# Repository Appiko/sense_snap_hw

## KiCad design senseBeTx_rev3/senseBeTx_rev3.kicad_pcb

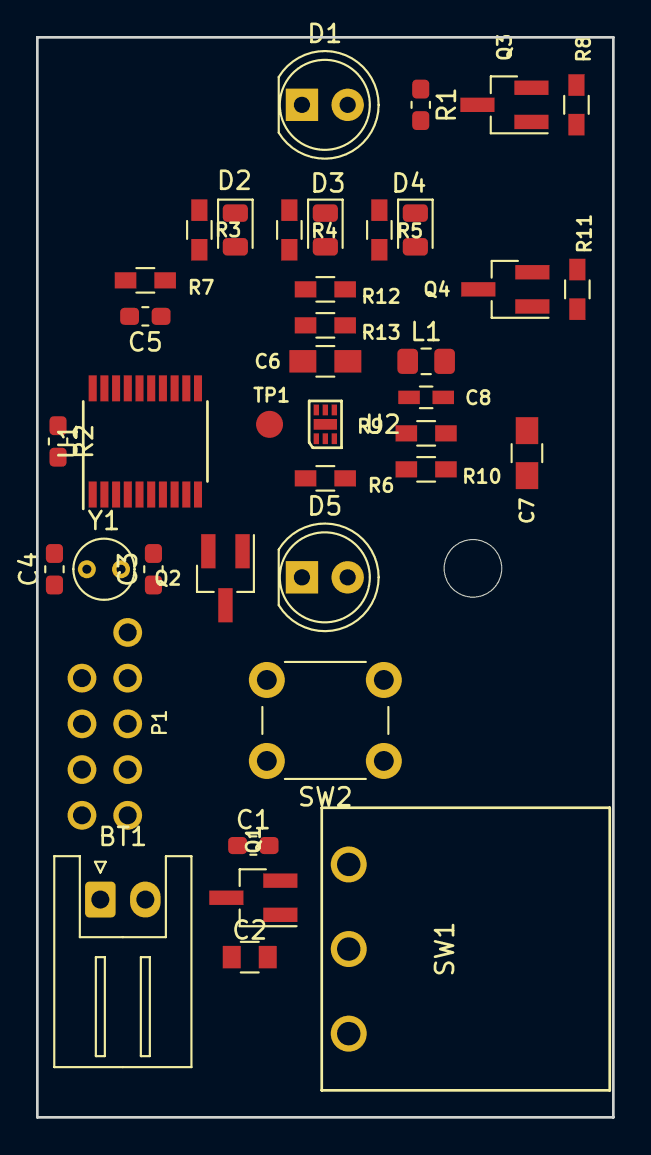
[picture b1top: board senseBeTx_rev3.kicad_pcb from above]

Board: 2 copper layers, 32.0 x 60.0 mm, 41 parts (1 on the bottom side), 30 nets, no tracks yet.

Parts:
BT1: Battery; 2462_BatteryHolder_AAx2
BT1#2: Battery; JST_XH_S02B-XH-A_1x02_P2.50mm_Horizontal
C1, C5: 100nF; C_0603_1608Metric_Pad1.05x0.95mm_HandSolder
C2: 10uF; C_0805
C3, C4: 8pF; C_0603_1608Metric_Pad1.05x0.95mm_HandSolder
C6: 22u; C_0805_HandSoldering
C7: 10u; C_0805_HandSoldering
C8: 22p; C_0603_HandSoldering
D1: D_Photo; LED_D5.0mm
D2, D3, D4: LED; LED_0805_2012Metric
D5: LED; LED_D5.0mm
L1: 22u; L_0805_2012Metric_Pad1.15x1.40mm_HandSolder
MK1: Mounting_Hole; MountingHole_3.2mm_M3
P1: CONN_02X05; prog_connect_2x3
Q1: SI2301; SOT-23_Handsoldering
Q2, Q3, Q4: SI2302; SOT-23_Handsoldering
R1, R2: 100k; R_0603_1608Metric_Pad1.05x0.95mm_HandSolder
R3, R4, R5: 100E; R_0603_HandSoldering
R6, R7, R8, R10, R11: 470k; R_0603_HandSoldering
R9: 510k; R_0603_HandSoldering
R12: 4.7M; R_0603_HandSoldering
R13: 1.2M; R_0603_HandSoldering
SW1: Switch_SW_SPST; SlideSwitch_1P2T_RightAngle
SW2: SW_Push_Dual; SW_PUSH_6mm
TP1: FB_TP; Measurement_Point_Round-SMD-Pad_Small
U1: STM32L011F3Px; TSSOP-20_4.4x6.5mm_P0.65mm
U2: AP3403; AP3403_U-DFN1616-6(Type G)
Y1: Crystal; Crystal_C38-LF_d3.0mm_l8.0mm_Vertical

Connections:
/BUTTON: C1.1, SW2.2, U1.7
/IR_LED_EN: Q2.1, R7.1, U1.18
/LED_RED_1: R3.2, U1.9
/LED_RED_2: R4.2, U1.10
/LED_RED_3: R5.2, U1.11
/LIGHT_SENSE: D1.2, R1.1, U1.6
/PWR1: Q3.1, R8.1, U1.13
/PWR2: Q4.1, R11.1, U1.17
/RCC_OSC32_IN: C4.1, U1.2, Y1.1
/RCC_OSC32_OUT: C3.1, U1.3, Y1.2
/REG_EN: R6.1, U1.12, U2.1
/RESET: P1.5, U1.4
/SENSE_CONTROL: D1.1, U1.14
/SYS_SWDCLK: P1.3, U1.20
/SYS_SWDIO: P1.1, U1.19
/USART2_TX: P1.2, U1.8
/VLED: C7.1, C8.1, D5.2, L1.2, R9.1
GND: BT1#2.2, C1.2, C2.2, C3.2, C4.2, C5.1, C6.2, C7.2, D2.1, D3.1, D4.1, P1.6, Q1.1, Q2.2, Q3.2, Q4.2, R1.2, R2.1, R6.2, R7.2, R8.2, R10.2, R11.2, SW1.1, SW2.1, U1.15, U2.2, U2.3
unnamed: BT1#2.1, SW1.3
unnamed: C8.2, R9.2, R10.1, R12.1, R13.1, TP1.1, U2.6
unnamed: D2.2, R3.1
unnamed: D3.2, R4.1
unnamed: D4.2, R5.1
unnamed: D5.1, Q2.3
unnamed: L1.1, U2.4
unnamed: Q1.3, SW1.2
unnamed: Q3.3, R12.2
unnamed: Q4.3, R13.2
unnamed: R2.2, U1.1
VDD: C2.1, C5.2, C6.1, P1.4, Q1.2, U1.5, U1.16, U2.5

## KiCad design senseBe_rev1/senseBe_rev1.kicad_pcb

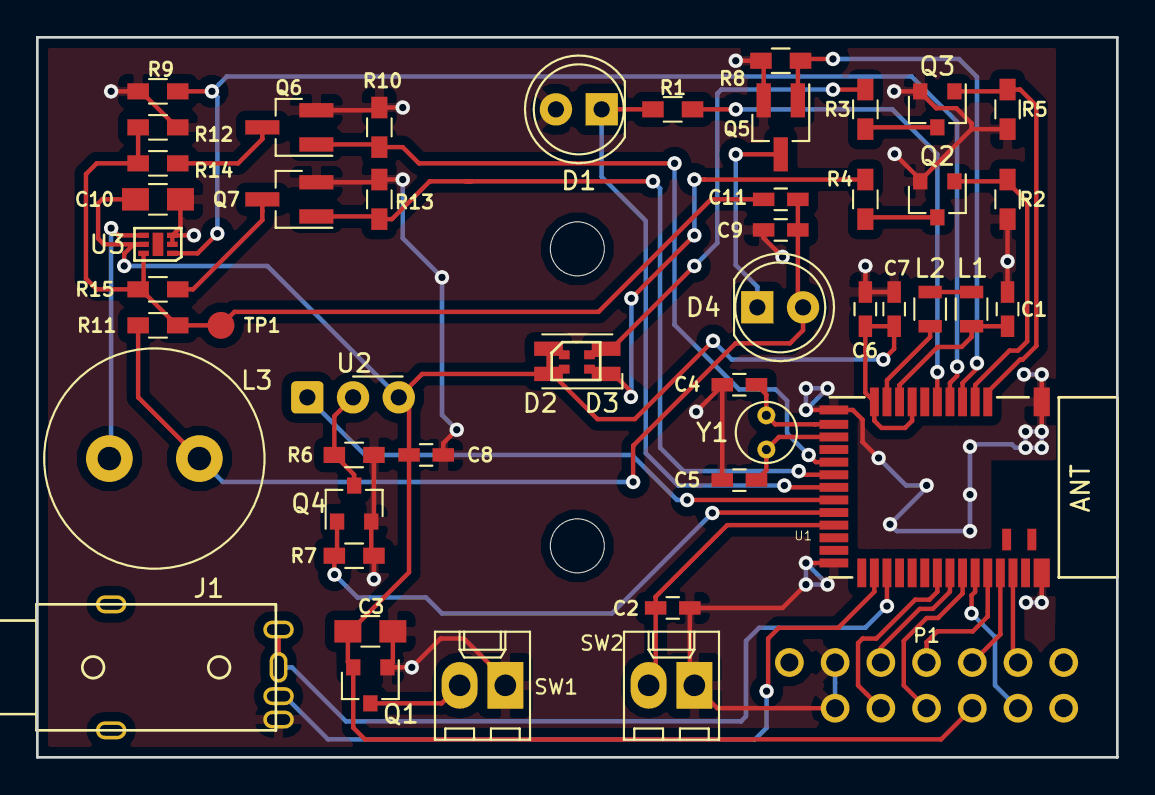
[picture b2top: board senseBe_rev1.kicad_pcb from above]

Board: 2 copper layers, 60.0 x 40.0 mm, 52 parts (1 on the bottom side), 39 nets.

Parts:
BT1: Battery; 2462_BatteryHolder_AAx2
C1, C6: 1uF; C_0603_HandSoldering
C2, C7, C8: 100nF; C_0603_HandSoldering
C3: 10uF; C_0805_HandSoldering
C4, C5: 8pF; C_0603_HandSoldering
C9: 10u; C_0603_HandSoldering
C10: 22u; C_0805_HandSoldering
C11: 8p; C_0603_HandSoldering
D1: D_Photo; LED_D5.0mm
D2: 18-225/R6G6C-A01/3T; 18-225_R6G6C-A01_3T
D3: APBD3224SURKCGKC; LED_APBD3224SURKCGKC-F01
D4: SFH4545; LED_D5.0mm
J1: PJ-32434_3-5mmAudioJack; PJ-32434-3_5mm-AudioJack
L1: 15nH; L_0805
L2: 10nH; L_0805
L3: 22u; L_Radial_D12.0mm_P5.00mm_Fastron_11P
MK1, MK2: Mounting_Hole; MountingHole_3mm
P1: CONN_02X05; prog_connect
Q1: TSM2301; SOT-23
Q2, Q3, Q4: SI2302; SOT-23
Q5, Q6, Q7: SI2302; SOT-23_Handsoldering
R1: 100k; R_0603_HandSoldering
R2, R5, R7, R8, R9, R10, R11, R12, R13: 470k; R_0603_HandSoldering
R3: 33; R_0603_HandSoldering
R4: 24; R_0603_HandSoldering
R6, R14: 3.9M; R_0603_HandSoldering
R15: 1.2M; R_0603_HandSoldering
SW1: SW_SPST; Molex_KK-6410-02_02x2.54mm_Straight
SW2: SW_DPST; Molex_KK-6410-02_02x2.54mm_Straight
TP1: FB_TP; Measurement_Point_Round-SMD-Pad_Small
U1: MDBT42Q; mdbt42Q
U2: TSSP4056; Vishay_MINIMOLD-3Pin
U3: AP3403; AP3403_U-DFN1616-6(Type G)
Y1: T38 Mercury; Crystal_C38-LF_D3.0mm_L8.0mm_Vertical

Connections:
/BUTTON: C2.2, SW2.2, U1.21
/DCC: L2.2, U1.10
/DEC4: C1.2, L1.1, U1.9
/FOCUS: J1.3, U1.26
/GPIO1: P1.6, U1.33
/GPIO2: P1.7, U1.32
/IR_LED_EN: Q5.1, R8.1, U1.4
/LED_GREEN: Q3.1, R5.1, U1.2
/LED_RED: Q2.1, R2.1, U1.3
/LFCLK_XL1: C4.2, U1.13, Y1.1
/LFCLK_XL2: C5.2, U1.14, Y1.2
/LIGHT_SENSE: D1.1, R1.2, U1.18
/LIGHT_SENSE_EN: R1.1, U1.6
/PWR1: Q6.1, R10.1, U1.16
/PWR2: Q7.1, R13.1, U1.17
/REG_EN: R9.1, U1.5, U3.1
/RESET: P1.5, U1.35
/RX: P1.8, U1.31
/RX_EN: Q4.1, R7.1, U1.20
/RX_OUT: U1.19, U2.1
/SWDCLK: P1.3, U1.36
/SWDIO: P1.1, U1.37
/Sheet5C63BFE7/VLED: C9.1, C11.1, D4.2, L3.2, R11.1
/TRIGGER: J1.2, J1.4, U1.27
/TX: P1.2, U1.34
GND: C1.1, C2.1, C3.2, C4.1, C5.1, C6.1, C7.1, C8.2, C9.2, C10.2, D1.2, J1.1, P1.9, P1.10, Q1.1, Q2.2, Q3.2, Q4.2, Q5.2, Q6.2, Q7.2, R2.2, R5.2, R6.2, R7.2, R8.2, R9.2, R10.2, R12.2, R13.2, SW1.1, SW2.1, U1.1, U1.12, U1.24, U1.39, U3.2, U3.3
unnamed: C11.2, R11.2, R12.1, R14.1, R15.1, TP1.1, U3.6
unnamed: D2.2, D3.4, R3.2
unnamed: D2.4, D3.2, R4.2
unnamed: D4.1, Q5.3
unnamed: L1.2, L2.1
unnamed: L3.1, U3.4
unnamed: Q1.3, SW1.2
unnamed: Q2.3, R4.1
unnamed: Q3.3, R3.1
unnamed: Q4.3, R6.1, U2.2
unnamed: Q6.3, R14.2
unnamed: Q7.3, R15.2
VDD: C3.1, C6.2, C7.2, C8.1, C10.1, D2.1, D2.3, D3.1, D3.3, P1.4, Q1.2, U1.8, U1.11, U2.3, U3.5

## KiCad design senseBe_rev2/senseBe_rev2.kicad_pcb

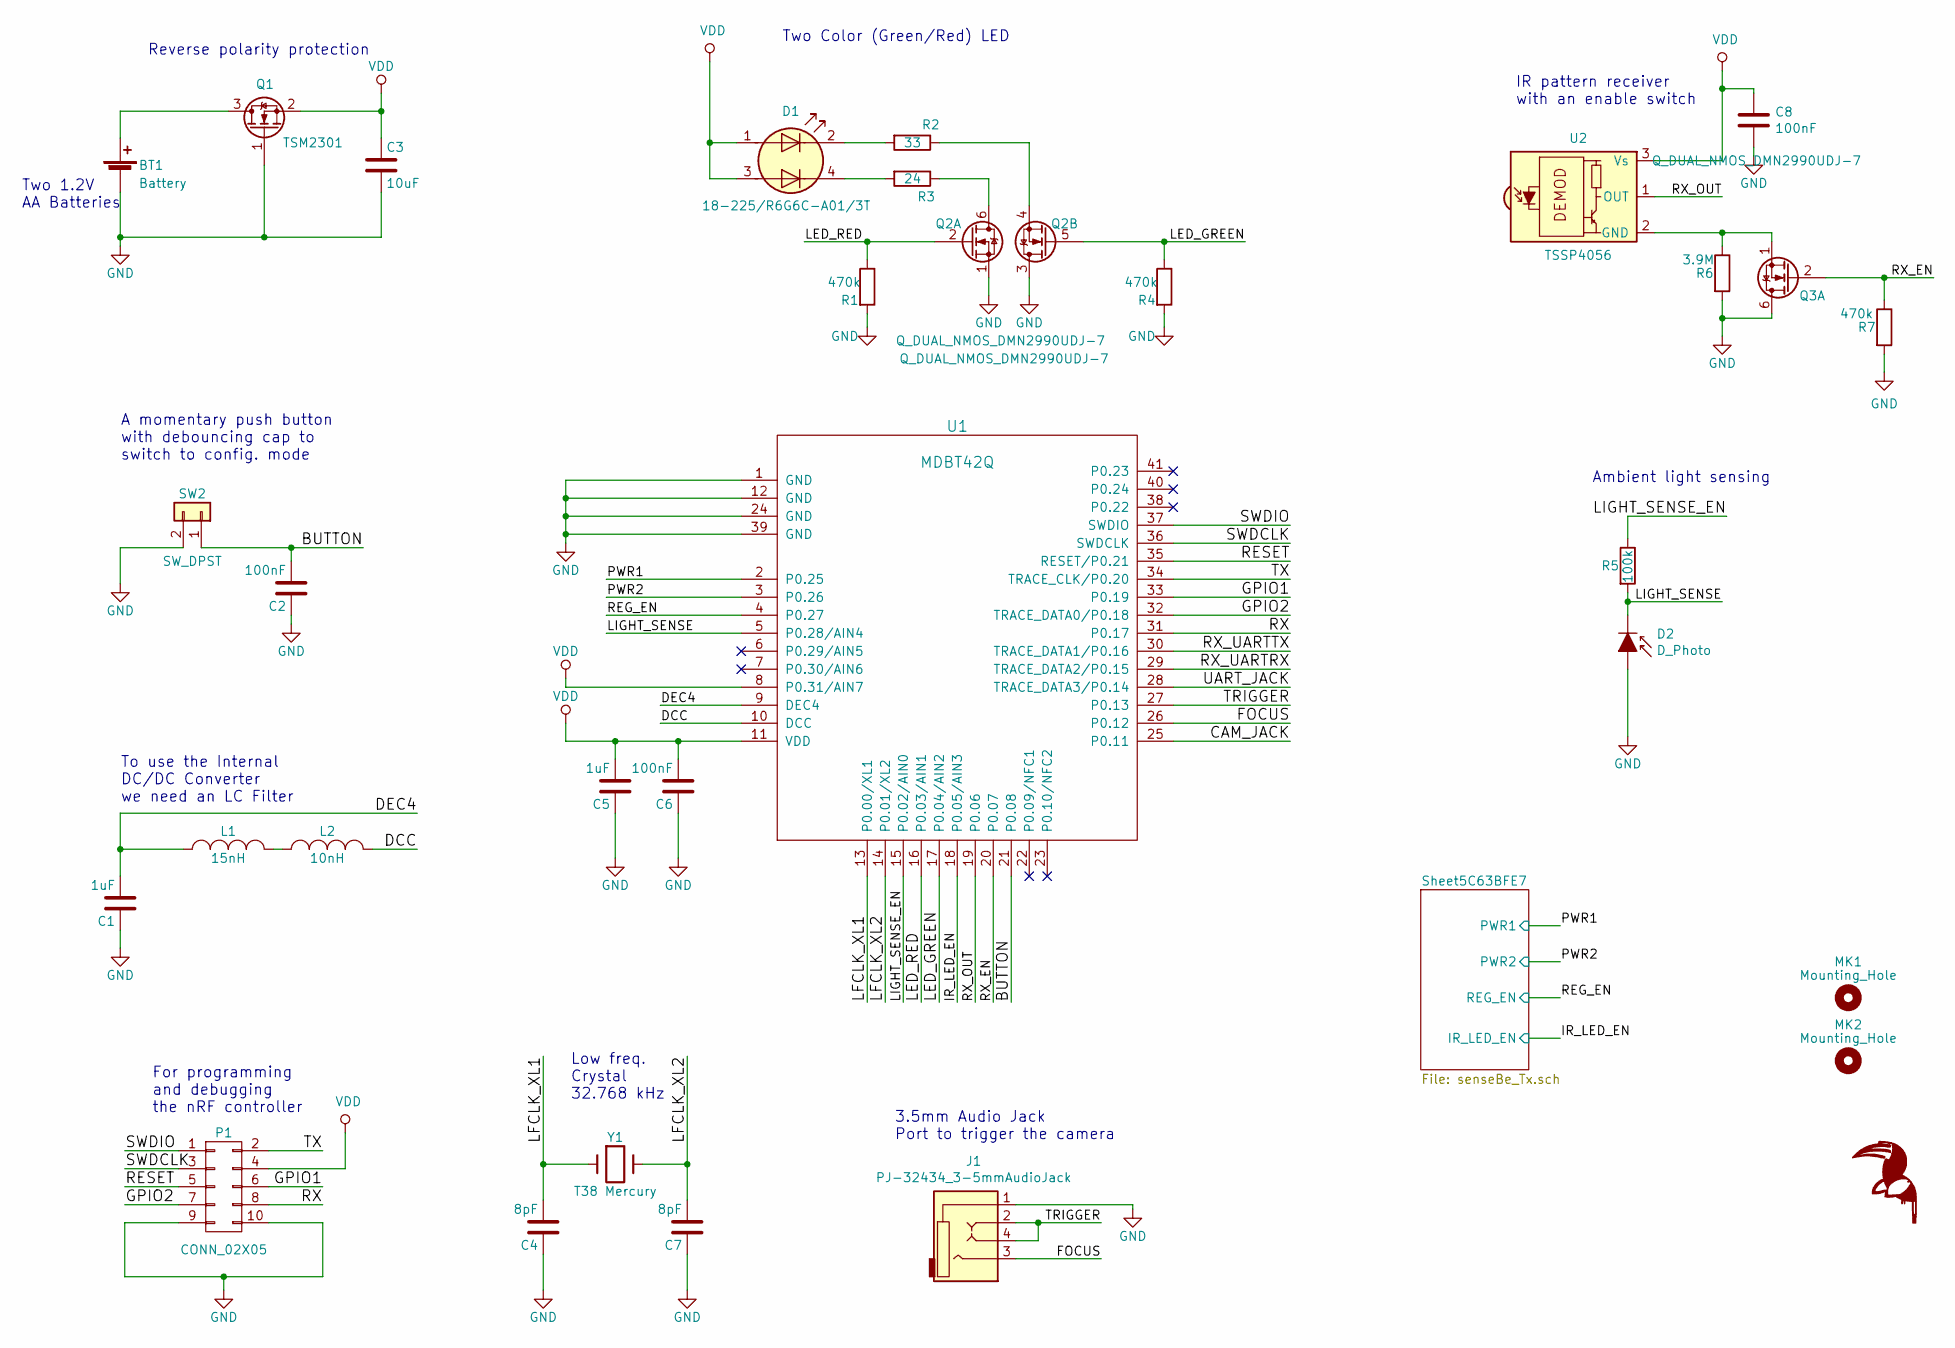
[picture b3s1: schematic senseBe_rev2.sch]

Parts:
BT1: Battery; Molex_KK-6410-02_02x2.54mm_Straight
C1, C5: 1uF; C_0603_HandSoldering
C2, C6, C8: 100nF; C_0603_HandSoldering
C3: 10uF; C_0805_HandSoldering
C4, C7: 8pF; C_0603_HandSoldering
D1: 18-225/R6G6C-A01/3T; 18-225_R6G6C-A01_3T
D2: D_Photo; LED_D5.0mm
J1: PJ-32434_3-5mmAudioJack; PJ-32434-3_5mm-AudioJack
L1: 15nH; L_0805
L2: 10nH; L_0805
MK1, MK2: Mounting_Hole; MountingHole_3mm
P1: CONN_02X05; prog_connect
Q1: TSM2301; SOT-23
Q2, Q3: Q_DUAL_NMOS_DMN2990UDJ-7; DMN2990UDJ-7
R1, R4, R7: 470k; R_0603_HandSoldering
R2: 33; R_0603_HandSoldering
R3: 24; R_0603_HandSoldering
R5: 100k; R_0603_HandSoldering
R6: 3.9M; R_0603_HandSoldering
SW2: SW_DPST; Molex_KK-6410-02_02x2.54mm_Straight
U1: MDBT42Q; mdbt42Q
U2: TSSP4056; Vishay_MINIMOLD-3Pin
Y1: T38 Mercury; Crystal_C38-LF_D3.0mm_L8.0mm_Vertical

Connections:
/BUTTON: C2.2, SW2.1, U1.21 (P0.08)
/CAM_JACK: U1.25 (P0.11)
/DCC: L2.2, U1.10 (DCC)
/DEC4: C1.2, L1.1, U1.9 (DEC4)
/FOCUS: J1.3, U1.26 (P0.12)
/GPIO1: P1.6, U1.33 (P0.19)
/GPIO2: P1.7, U1.32 (TRACE_DATA0/P0.18)
/IR_LED_EN: U1.18 (P0.05/AIN3); also elsewhere on the board
/LED_GREEN: Q2.5 (G), R4.1, U1.17 (P0.04/AIN2)
/LED_RED: Q2.2 (G), R1.1, U1.16 (P0.03/AIN1)
/LFCLK_XL1: C4.2, U1.13 (P0.00/XL1), Y1.1
/LFCLK_XL2: C7.2, U1.14 (P0.01/XL2), Y1.2
/LIGHT_SENSE: D2.1 (K), R5.2, U1.5 (P0.28/AIN4)
/LIGHT_SENSE_EN: R5.1, U1.15 (P0.02/AIN0)
/PWR1: U1.2 (P0.25); also elsewhere on the board
/PWR2: U1.3 (P0.26); also elsewhere on the board
/REG_EN: U1.4 (P0.27); also elsewhere on the board
/RESET: P1.5, U1.35 (RESET/P0.21)
/RX: P1.8, U1.31 (P0.17)
/RX_EN: Q3.2 (G), R7.1, U1.20 (P0.07)
/RX_OUT: U1.19 (P0.06), U2.1 (OUT)
/RX_UARTRX: U1.29 (TRACE_DATA2/P0.15)
/RX_UARTTX: U1.30 (TRACE_DATA1/P0.16)
/SWDCLK: P1.3, U1.36 (SWDCLK)
/SWDIO: P1.1, U1.37 (SWDIO)
/TRIGGER: J1.2, J1.4, U1.27 (P0.13)
/TX: P1.2, U1.34 (TRACE_CLK/P0.20)
/UART_JACK: U1.28 (TRACE_DATA3/P0.14)
GND: BT1.2 (-), C1.1, C2.1, C3.2, C4.1, C5.1, C6.1, C7.1, C8.2, D2.2 (A), J1.1, P1.9, P1.10, Q1.1 (G), Q2.1 (S), Q2.3 (D), Q3.6 (D), R1.2, R4.2, R6.2, R7.2, SW2.2, U1.1 (GND), U1.12 (GND), U1.24 (GND), U1.39 (GND); also elsewhere on the board
unnamed: BT1.1 (+), Q1.3 (D)
unnamed: D1.2 (K1), R2.2
unnamed: D1.4 (K2), R3.2
unnamed: L1.2, L2.1
unnamed: Q2.4 (S), R2.1
unnamed: Q2.6 (D), R3.1
unnamed: Q3.1 (S), R6.1, U2.2 (GND)
VDD: C3.1, C5.2, C6.2, C8.1, D1.1 (A1), D1.3 (A2), P1.4, Q1.2 (S), U1.8 (P0.31/AIN7), U1.11 (VDD), U2.3 (Vs); also elsewhere on the board

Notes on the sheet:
Two 1.2V AA Batteries
Reverse polarity protection
Two Color (Green/Red) LED
A momentary push button with debouncing cap to switch to config. mode
To use the Internal DC/DC Converter we need an LC Filter
For programming and debugging the nRF controller
Low freq. Crystal 32.768 kHz
IR pattern receiver with an enable switch
Ambient light sensing
3.5mm Audio Jack Port to trigger the camera

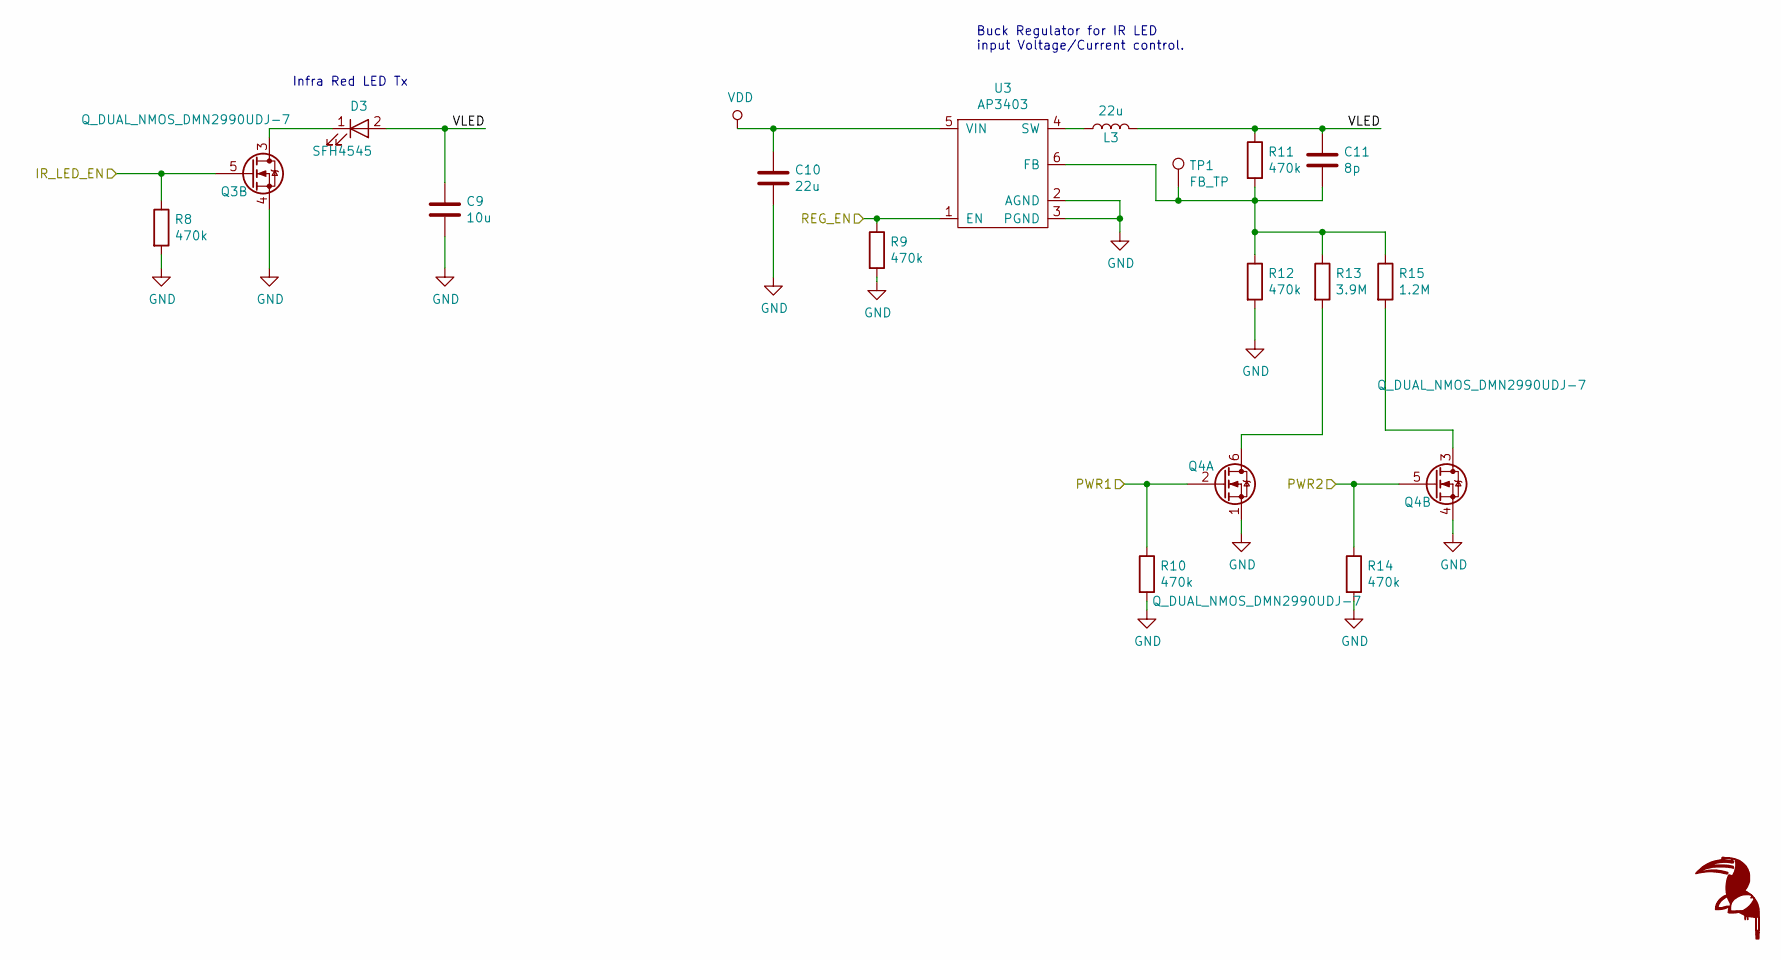
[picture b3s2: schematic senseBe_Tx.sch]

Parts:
C9: 10u; C_0603_HandSoldering
C10: 22u; C_0805_HandSoldering
C11: 8p; C_0805_HandSoldering
D3: SFH4545; LED_D5.0mm
L3: 22u; L_Radial_D12.0mm_P5.00mm_Fastron_11P
Q3, Q4: Q_DUAL_NMOS_DMN2990UDJ-7; DMN2990UDJ-7
R8, R9, R10, R11, R12, R14: 470k; R_0603_HandSoldering
R13: 3.9M; R_0603_HandSoldering
R15: 1.2M; R_0603_HandSoldering
TP1: FB_TP; Measurement_Point_Round-SMD-Pad_Small
U3: AP3403; AP3403_U-DFN1616-6(Type G)

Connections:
/IR_LED_EN: Q3.5 (G), R8.1; also elsewhere on the board
/PWR1: Q4.2 (G), R10.1; also elsewhere on the board
/PWR2: Q4.5 (G), R14.1; also elsewhere on the board
/REG_EN: R9.1, U3.1 (EN); also elsewhere on the board
/Sheet5C63BFE7/VLED: C9.1, C11.1, D3.2 (A), L3.2, R11.1
GND: C9.2, C10.2, Q3.4 (S), Q4.1 (S), Q4.4 (S), R8.2, R9.2, R10.2, R12.2, R14.2, U3.2 (AGND), U3.3 (PGND); also elsewhere on the board
unnamed: C11.2, R11.2, R12.1, R13.1, R15.1, TP1.1, U3.6 (FB)
unnamed: D3.1 (K), Q3.3 (D)
unnamed: L3.1, U3.4 (SW)
unnamed: Q4.3 (D), R15.2
unnamed: Q4.6 (D), R13.2
VDD: C10.1, U3.5 (VIN); also elsewhere on the board

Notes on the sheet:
Infra Red LED Tx
Buck Regulator for IR LED input Voltage/Current control.

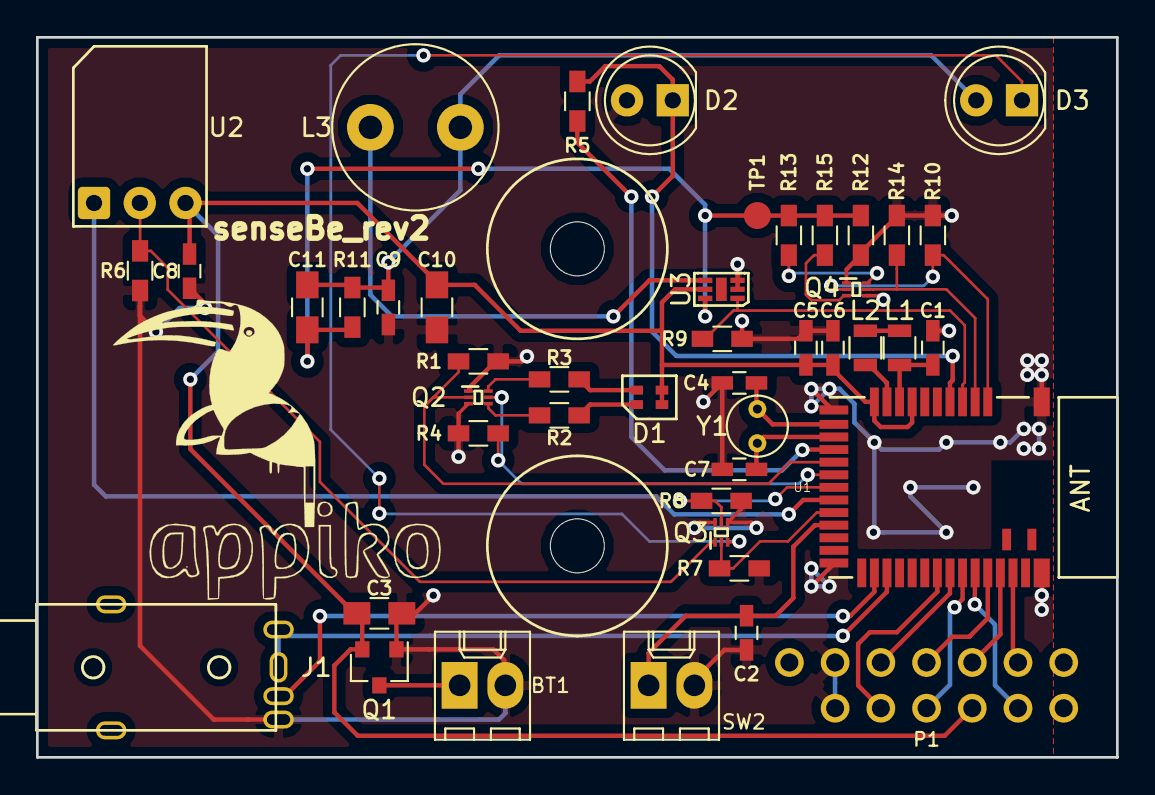
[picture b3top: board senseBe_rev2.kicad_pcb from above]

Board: 2 copper layers, 60.0 x 40.0 mm, 47 parts (0 on the bottom side), 39 nets.

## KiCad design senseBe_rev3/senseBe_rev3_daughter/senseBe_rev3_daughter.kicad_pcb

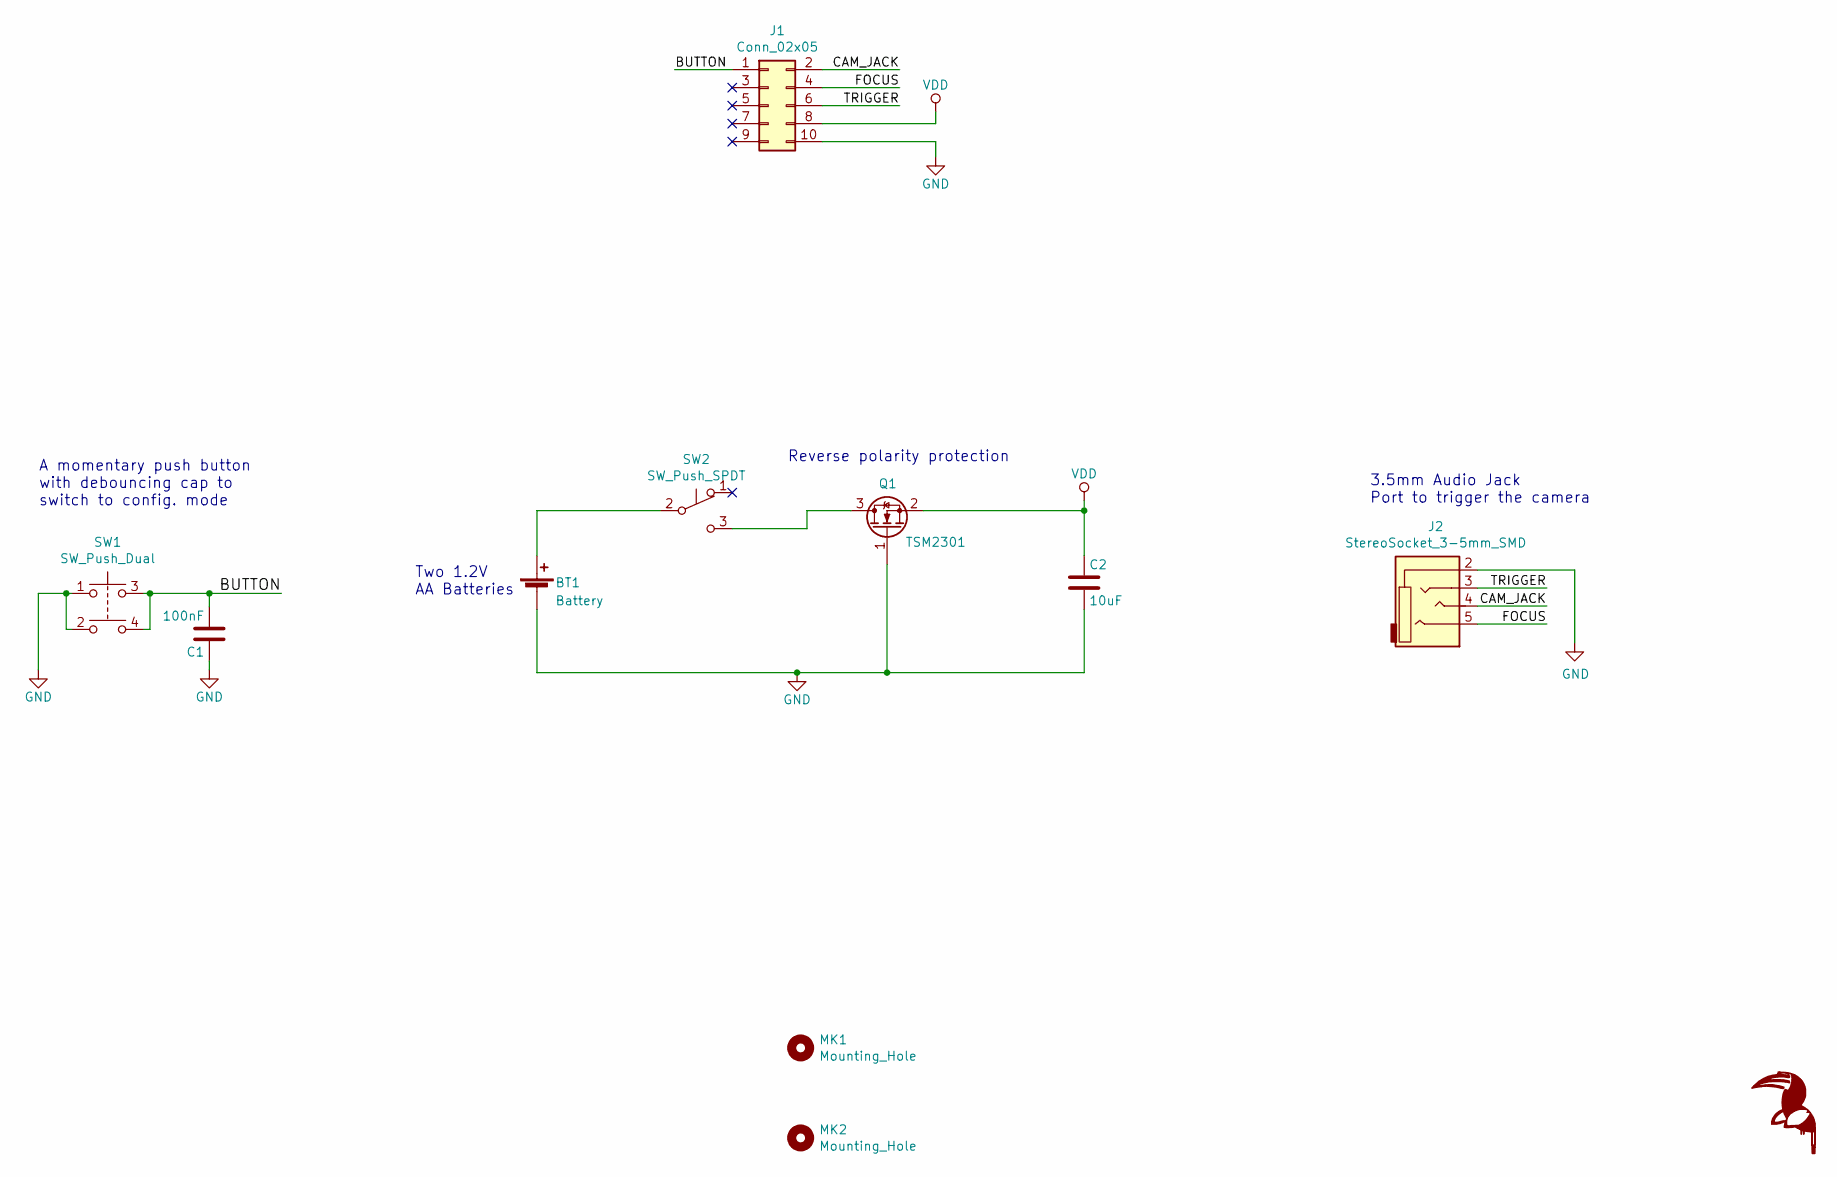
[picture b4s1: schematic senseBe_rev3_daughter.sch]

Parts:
BT1: Battery; Molex_KK-6410-02_02x2.54mm_Straight
C1: 100nF; C_0603_HandSoldering
C2: 10uF; C_0805_HandSoldering
J1: Conn_02x05; PinHeader_2x05_P2.54mm_Vertical
J2: StereoSocket_3-5mm_SMD; Audio_Jack_3.5mm_Horizontal_SMD
MK1, MK2: Mounting_Hole; MountingHole_3mm
Q1: TSM2301; SOT-23
SW1: SW_Push_Dual; RightAngle_Tactile_Push_Button
SW2: SW_Push_SPDT; SlideSwitch_1P2T_RightAngle

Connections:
/BUTTON: C1.2, J1.1, SW1.3, SW1.4
/CAM_JACK: J1.2, J2.4
/FOCUS: J1.4, J2.5
/TRIGGER: J1.6, J2.3
GND: BT1.2 (-), C1.1, C2.2, J1.10, J2.2, Q1.1 (G), SW1.1, SW1.2
unnamed: BT1.1 (+), SW2.2 (B)
unnamed: Q1.3 (D), SW2.3 (C)
VDD: C2.1, J1.8, Q1.2 (S)

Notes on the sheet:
Two 1.2V AA Batteries
Reverse polarity protection
A momentary push button with debouncing cap to switch to config. mode
3.5mm Audio Jack Port to trigger the camera

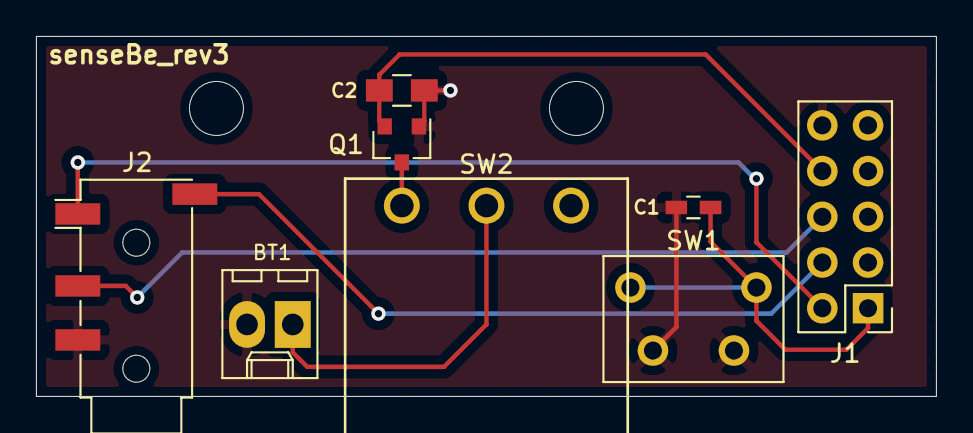
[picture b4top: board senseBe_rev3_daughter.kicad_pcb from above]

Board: 2 copper layers, 50.0 x 20.0 mm, 10 parts (0 on the bottom side), 8 nets.

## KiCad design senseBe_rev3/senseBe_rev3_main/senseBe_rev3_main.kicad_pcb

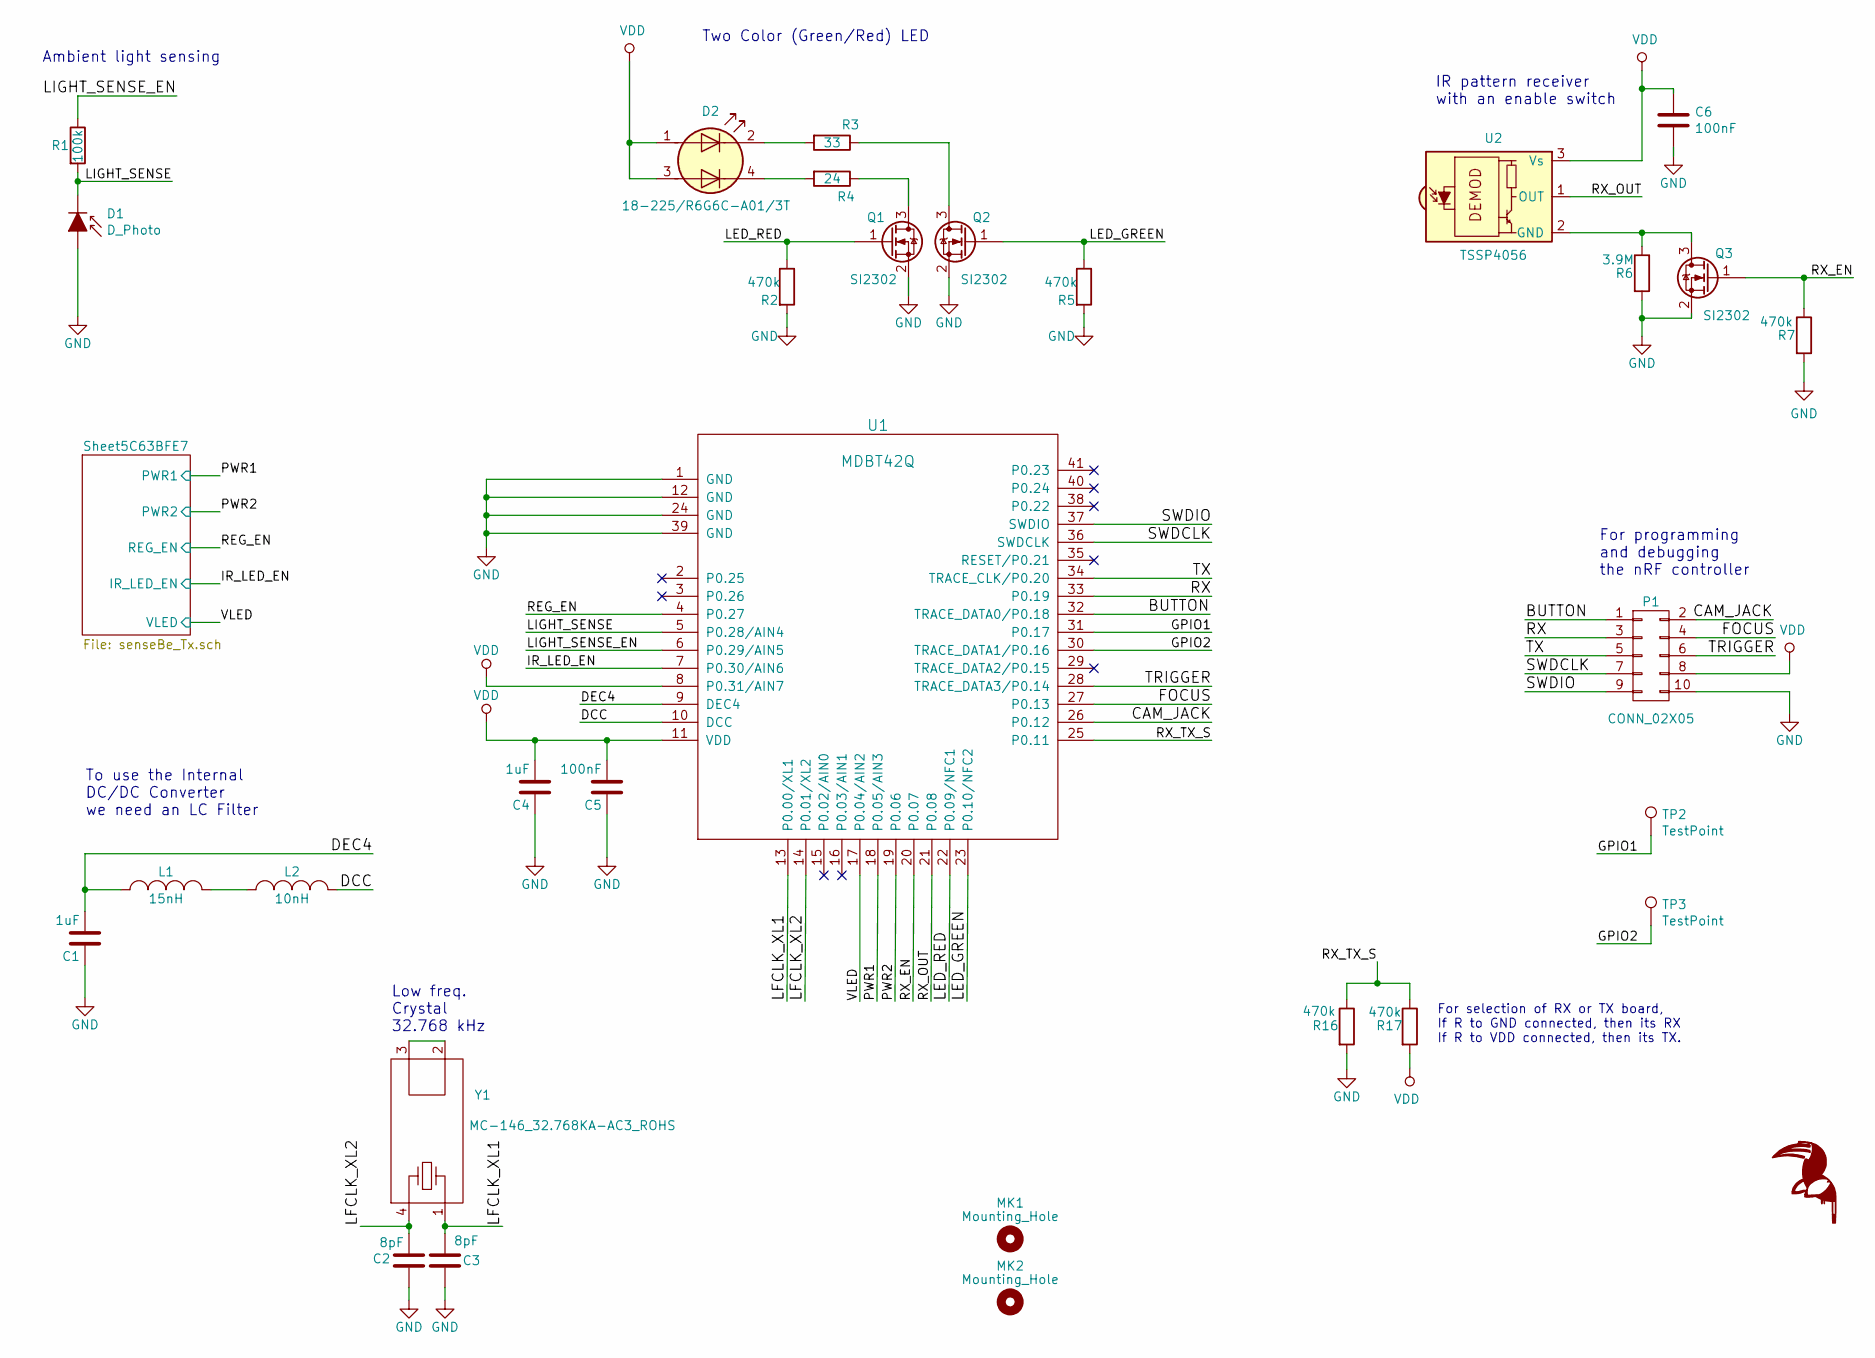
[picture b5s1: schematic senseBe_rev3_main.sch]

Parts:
C1, C4: 1uF; C_0603_HandSoldering
C2, C3: 8pF; C_0603_HandSoldering
C5, C6: 100nF; C_0603_HandSoldering
D1: D_Photo; LED_D5.0mm
D2: 18-225/R6G6C-A01/3T; 18-225_R6G6C-A01_3T
L1: 15nH; L_0805
L2: 10nH; L_0805
MK1, MK2: Mounting_Hole; MountingHole_2.5mm
P1: CONN_02X05; PinHeader_2x05_P2.54mm_Vertical
Q1, Q2, Q3: SI2302; SOT-23
R1: 100k; R_0603_HandSoldering
R2, R5, R7, R16, R17: 470k; R_0603_HandSoldering
R3: 33; R_0603_HandSoldering
R4: 24; R_0603_HandSoldering
R6: 3.9M; R_0603_HandSoldering
TP2, TP3: TestPoint; Measurement_Point_Round-SMD-Pad_Small
U1: MDBT42Q; mdbt42Q
U2: TSSP4056; Vishay_MINIMOLD-3Pin
Y1: MC-146_32.768KA-AC3_ROHS; Crystal_SMD_SeikoEpson_MC146-4Pin_6.7x1.5mm_HandSoldering

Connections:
/BUTTON: P1.1, U1.32 (TRACE_DATA0/P0.18)
/CAM_JACK: P1.2, U1.26 (P0.12)
/DCC: L2.2, U1.10 (DCC)
/DEC4: C1.2, L1.1, U1.9 (DEC4)
/FOCUS: P1.4, U1.27 (P0.13)
/GPIO1: TP2.1, U1.31 (P0.17)
/GPIO2: TP3.1, U1.30 (TRACE_DATA1/P0.16)
/IR_LED_EN: U1.7 (P0.30/AIN6); also elsewhere on the board
/LED_GREEN: Q2.1 (G), R5.1, U1.23 (P0.10/NFC2)
/LED_RED: Q1.1 (G), R2.1, U1.22 (P0.09/NFC1)
/LFCLK_XL1: C3.2, U1.13 (P0.00/XL1), Y1.1
/LFCLK_XL2: C2.2, U1.14 (P0.01/XL2), Y1.4
/LIGHT_SENSE: D1.1 (K), R1.2, U1.5 (P0.28/AIN4)
/LIGHT_SENSE_EN: R1.1, U1.6 (P0.29/AIN5)
/PWR1: U1.18 (P0.05/AIN3); also elsewhere on the board
/PWR2: U1.19 (P0.06); also elsewhere on the board
/REG_EN: U1.4 (P0.27); also elsewhere on the board
/RX: P1.3, U1.33 (P0.19)
/RX_EN: Q3.1 (G), R7.1, U1.20 (P0.07)
/RX_OUT: U1.21 (P0.08), U2.1 (OUT)
/RX_TX_S: R16.1, R17.1, U1.25 (P0.11)
/SWDCLK: P1.7, U1.36 (SWDCLK)
/SWDIO: P1.9, U1.37 (SWDIO)
/TRIGGER: P1.6, U1.28 (TRACE_DATA3/P0.14)
/TX: P1.5, U1.34 (TRACE_CLK/P0.20)
/VLED: U1.17 (P0.04/AIN2); also elsewhere on the board
GND: C1.1, C2.1, C3.1, C4.1, C5.1, C6.2, D1.2 (A), P1.10, Q1.2 (S), Q2.2 (S), Q3.2 (S), R2.2, R5.2, R6.2, R7.2, R16.2, U1.1 (GND), U1.12 (GND), U1.24 (GND), U1.39 (GND); also elsewhere on the board
unnamed: D2.2 (K1), R3.2
unnamed: D2.4 (K2), R4.2
unnamed: L1.2, L2.1
unnamed: Q1.3 (D), R4.1
unnamed: Q2.3 (D), R3.1
unnamed: Q3.3 (D), R6.1, U2.2 (GND)
unnamed: Y1.2, Y1.3
VDD: C4.2, C5.2, C6.1, D2.1 (A1), D2.3 (A2), P1.8, R17.2, U1.8 (P0.31/AIN7), U1.11 (VDD), U2.3 (Vs); also elsewhere on the board

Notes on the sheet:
Two Color (Green/Red) LED
To use the Internal DC/DC Converter we need an LC Filter
For programming and debugging the nRF controller
IR pattern receiver with an enable switch
Ambient light sensing
Low freq. Crystal 32.768 kHz
For selection of RX or TX board, If R to GND connected, then its RX If R to VDD connected, then its TX.

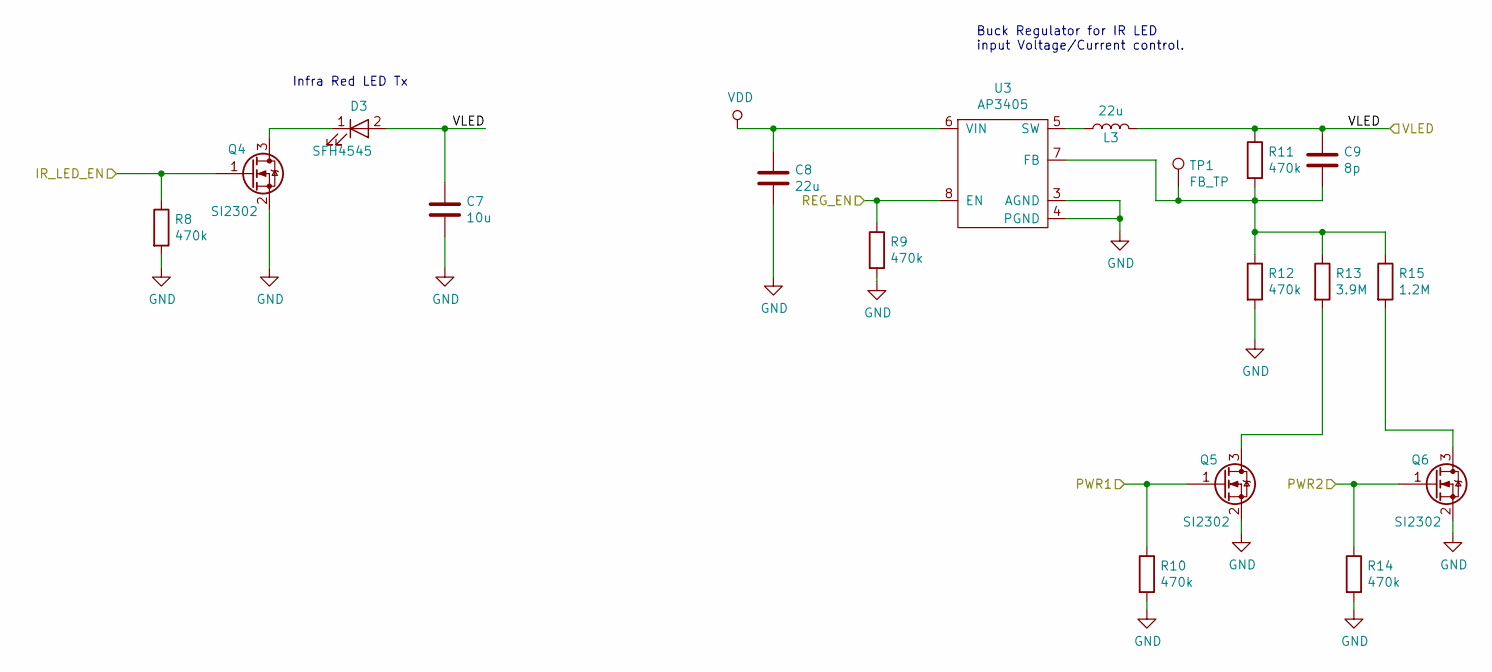
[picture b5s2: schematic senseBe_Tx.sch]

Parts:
C7: 10u; C_0603_HandSoldering
C8: 22u; C_0805_HandSoldering
C9: 8p; C_0805_HandSoldering
D3: SFH4545; LED_D5.0mm
L3: 22u; 22uH_SMD_5mm_Inductor
Q4, Q5, Q6: SI2302; SOT-23
R8, R9, R10, R11, R12, R14: 470k; R_0603_HandSoldering
R13: 3.9M; R_0603_HandSoldering
R15: 1.2M; R_0603_HandSoldering
TP1: FB_TP; Measurement_Point_Round-SMD-Pad_Small
U3: AP3405; AP3405_U-DFN2020-8

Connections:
/IR_LED_EN: Q4.1 (G), R8.1; also elsewhere on the board
/PWR1: Q5.1 (G), R10.1; also elsewhere on the board
/PWR2: Q6.1 (G), R14.1; also elsewhere on the board
/REG_EN: R9.1, U3.8 (EN); also elsewhere on the board
/VLED: C7.1, C9.1, D3.2 (A), L3.2, R11.1; also elsewhere on the board
GND: C7.2, C8.2, Q4.2 (S), Q5.2 (S), Q6.2 (S), R8.2, R9.2, R10.2, R12.2, R14.2, U3.3 (AGND), U3.4 (PGND); also elsewhere on the board
unnamed: C9.2, R11.2, R12.1, R13.1, R15.1, TP1.1, U3.7 (FB)
unnamed: D3.1 (K), Q4.3 (D)
unnamed: L3.1, U3.5 (SW)
unnamed: Q5.3 (D), R13.2
unnamed: Q6.3 (D), R15.2
VDD: C8.1, U3.6 (VIN); also elsewhere on the board

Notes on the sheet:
Infra Red LED Tx
Buck Regulator for IR LED input Voltage/Current control.

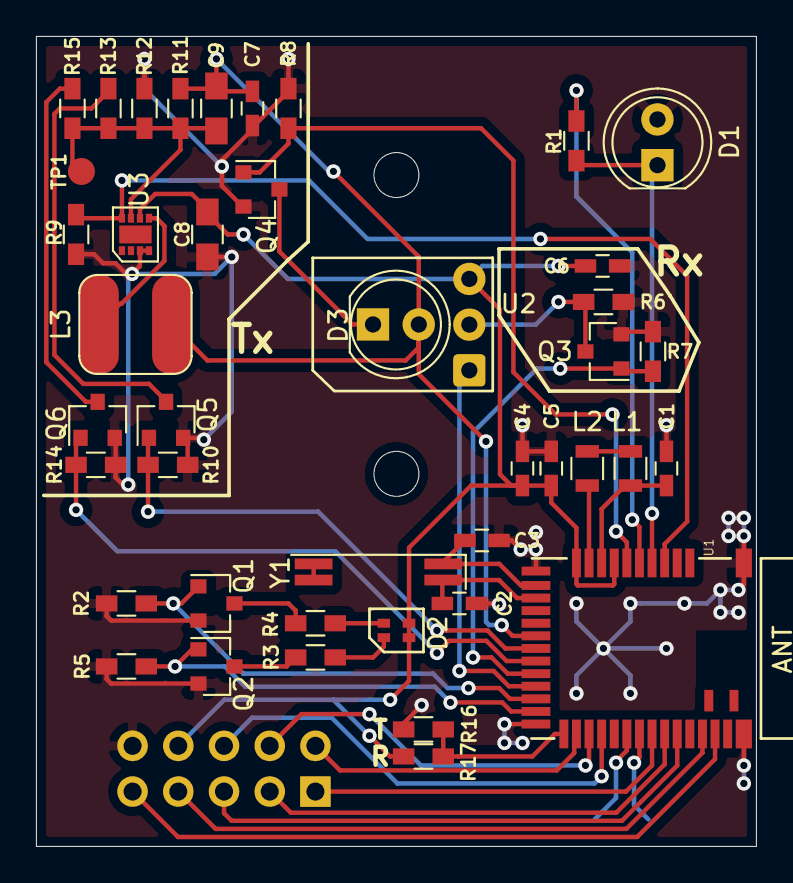
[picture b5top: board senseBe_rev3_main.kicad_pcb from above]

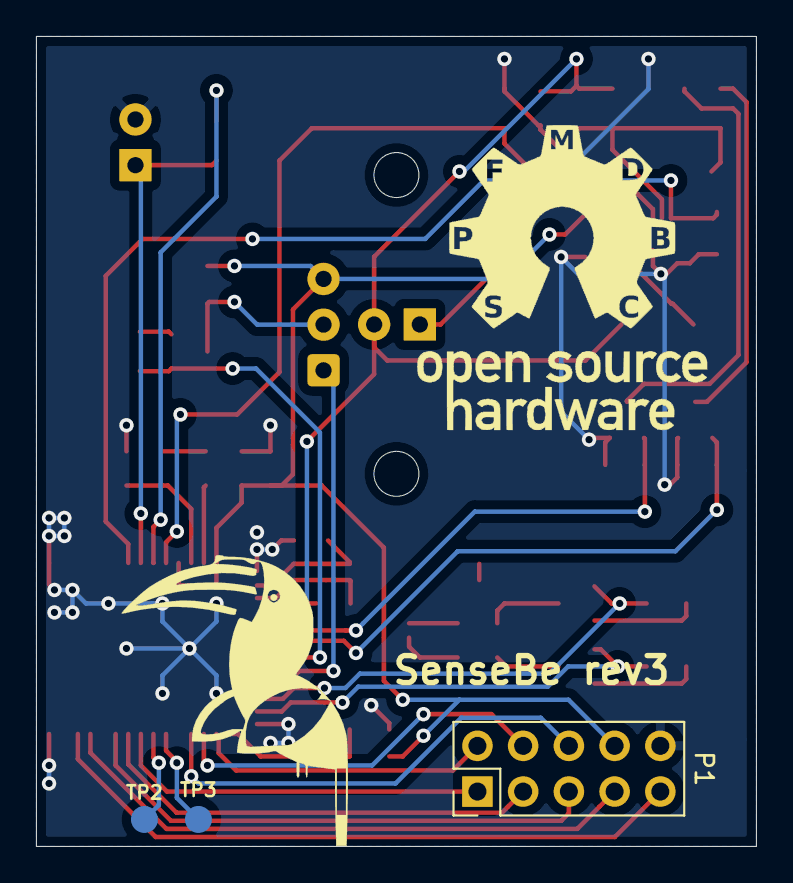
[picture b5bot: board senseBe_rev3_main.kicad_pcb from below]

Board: 2 copper layers, 40.0 x 45.0 mm, 48 parts (3 on the bottom side), 40 nets.
